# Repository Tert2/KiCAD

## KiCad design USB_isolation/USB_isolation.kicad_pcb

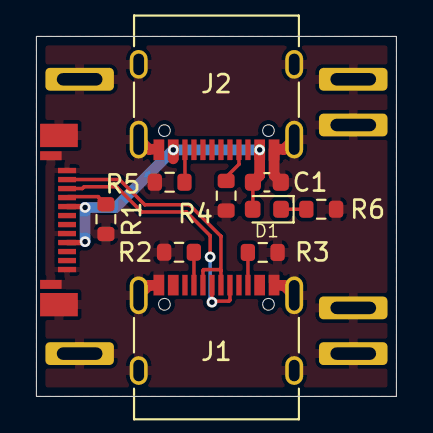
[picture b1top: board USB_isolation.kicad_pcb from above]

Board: 2 copper layers, 20.0 x 20.0 mm, 13 parts (0 on the bottom side), 10 nets.

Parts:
C1: 0.1u; C_0603_1608Metric
D1: LED_Small; LED_0603_1608Metric
J1, J2: USB_C_Receptacle_USB2.0_16P; USB_C_Receptacle_XKB_U262-16XN-4BVC11
J3: Conn_01x04_Pin; 4p
J8: Conn_01x02_Pin; 2p
R1, R2, R3, R4, R5, R6: 4.7k; R_0603_1608Metric
U1: UCAM001

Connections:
+5V: C1.1, D1.2 (A), J2.A4 (VBUS), J2.A9 (VBUS), J2.B4 (VBUS), J2.B9 (VBUS), U1.A4 (VBUS), U1.B9 (VBUS)
/D+: J1.A6 (D+), J1.B6 (D+), U1.A6 (D+)
/D-: J1.A7 (D-), J1.B7 (D-), U1.A7 (D-)
GND: C1.2, J1.A1 (GND), J1.A12 (GND), J1.B1 (GND), J1.B12 (GND), J1.S1 (SHIELD), J2.A1 (GND), J2.A12 (GND), J2.B1 (GND), J2.B12 (GND), J2.S1 (SHIELD), J3.1, J3.2, J3.3, J3.4, J8.1, J8.2, R1.2, R2.2, R3.2, R4.2, R5.2, R6.2, U1.A1 (GND), U1.A12 (GND), U1.B12 (GND), U1.S1 (SHIELD), U1.S2 (SHIELD)
unnamed: D1.1 (K), R6.1
unnamed: J1.A5 (CC1), R2.1
unnamed: J1.B5 (CC2), R3.1
unnamed: J2.A5 (CC1), R4.1
unnamed: J2.B5 (CC2), R5.1
unnamed: R1.1, U1.A5 (CC1)

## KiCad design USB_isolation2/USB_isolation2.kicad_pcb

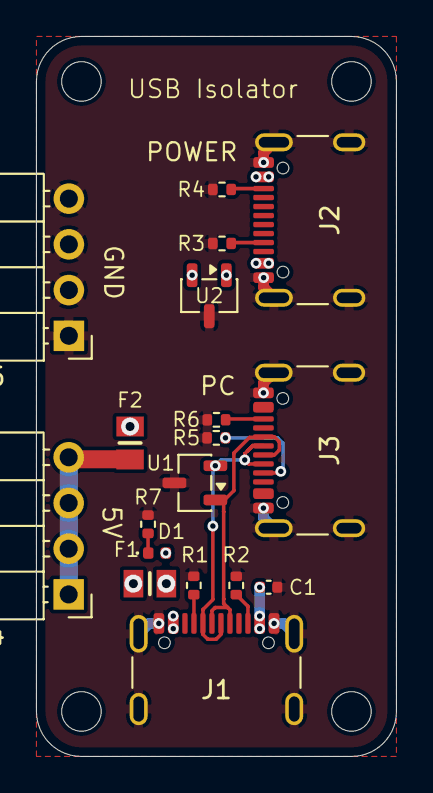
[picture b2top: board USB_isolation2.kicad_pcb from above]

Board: 2 copper layers, 20.0 x 40.0 mm, 18 parts (0 on the bottom side), 13 nets.

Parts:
C1: 4.7u; C_0402_1005Metric
D1: LED_Small; LED_0402_1005Metric
F1, F2: PICOSMDC110S-2; PICOSMDC010S2
J1, J2, J3: USB_C_Receptacle_USB2.0_16P; USB_C_Receptacle_GCT_USB4105-xx-A_16P_TopMnt_Horizontal
J4, J5: Conn_01x04_Pin; PinHeader_1x04_P2.54mm_Horizontal
R1, R2, R3, R4, R5, R6, R7: 4.7k; R_0402_1005Metric
U1, U2: SOT-23-3

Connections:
+5V: C1.1, D1.2 (A), F1.1, J1.A4 (VBUS), J1.A9 (VBUS), J1.B4 (VBUS), J1.B9 (VBUS)
D+: J1.A6 (D+), J1.B6 (D+), J3.A6 (D+), J3.B6 (D+), U1.1
D-: J1.A7 (D-), J1.B7 (D-), J3.A7 (D-), J3.B7 (D-), U1.2
GND: C1.2, J1.A1 (GND), J1.A12 (GND), J1.B1 (GND), J1.B12 (GND), J1.S1 (SHIELD), J2.A1 (GND), J2.A12 (GND), J2.B1 (GND), J2.B12 (GND), J2.S1 (SHIELD), J3.A1 (GND), J3.A12 (GND), J3.B1 (GND), J3.B12 (GND), J3.S1 (SHIELD), J5.1, J5.2, J5.3, J5.4, R1.2, R2.2, R3.2, R4.2, R5.2, R6.2, R7.2, U1.3, U2.3
unnamed: D1.1 (K), R7.1
unnamed: J1.A5 (CC1), R1.1
unnamed: J1.B5 (CC2), R2.1
unnamed: J2.A5 (CC1), R3.1
unnamed: J2.B5 (CC2), R4.1
unnamed: J3.A5 (CC1), R5.1
unnamed: J3.B5 (CC2), R6.1
unnamed: F2.2, J4.1, J4.2, J4.3, J4.4
VBUS: F1.2, F2.1, J2.A4 (VBUS), J2.A9 (VBUS), J2.B4 (VBUS), J2.B9 (VBUS), U2.1, U2.2

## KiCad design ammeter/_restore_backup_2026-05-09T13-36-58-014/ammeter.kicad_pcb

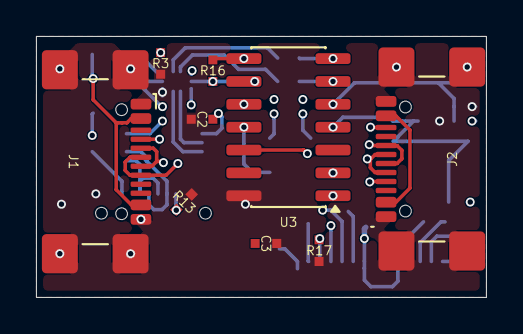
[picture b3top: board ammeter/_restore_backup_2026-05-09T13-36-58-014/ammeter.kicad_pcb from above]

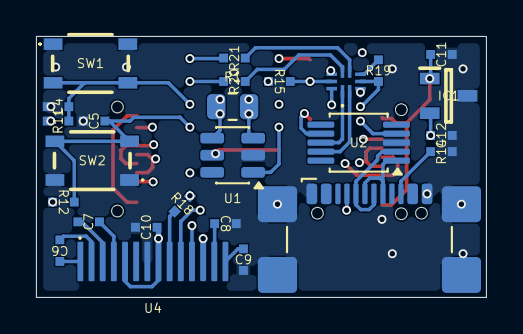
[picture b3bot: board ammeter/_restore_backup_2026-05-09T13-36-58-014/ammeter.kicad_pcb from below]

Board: 4 copper layers, 25.0 x 14.5 mm, 35 parts (26 on the bottom side), 36 nets.

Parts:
C2, C3, C4, C5: 0.1u; 1005
C6, C7, C8, C11: 1u; 1005
C9, C10: 4.7u; 1005
C12: 10u; 1005
IC1: AP7375-33SA-7; SOT96P240X110-3N
IC2: TMUXHS221NKGT
J1, J2, J3: USB_C_Receptacle_USB2.0_16P; USB_C_Receptacle_GCT_USB4110
R1: 8m; R_0805_2012Metric
R3, R11, R12, R18: 10k; R1005
R13, R14, R15, R16, R19, R20, R21: 4.7k; R1005
R17: 100k; R1005
SW1, SW2: SW_MEC_5E; SKRPABE010
U1: INA181; SOT-23-6
U2: CH340E; MSOP-10_3x3mm_P0.5mm
U3: ATtiny1604-SS; SOIC-14_3.9x8.7mm_P1.27mm
U4: X032-6032TSWAG02-H14 F

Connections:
+3V3: C2.1, C10.1, C12.1, IC1.2 (VOUT), IC2.9 (VCC), R11.2, R12.2, R15.2, R16.2, R18.2, U1.6 (V+), U2.7 (VCC), U2.10 (V3), U3.1 (VCC), U4.5 (VBAT), U4.8 (Vdd)
/#RTS: IC2.10 (SEL), U2.4 (~RTS)
/#res: R18.1, U4.9 (#RES)
/D+: J3.A6 (D+), J3.B6 (D+), U2.1 (UD+)
/D-: J3.A7 (D-), J3.B7 (D-), U2.2 (UD-)
/Rx: IC2.2 (D-), U2.9 (RXD)
/Rx3: R20.2, U3.6 (PB3)
/SCL: R15.1, U3.9 (PB0), U4.10 (SCL)
/SDA: R16.1, U3.8 (PB1), U4.11 (SDA)
/Tx: IC2.1 (D+), U2.8 (TXD)
/Tx2: R21.2, U3.7 (PB2)
/UPDI: IC2.4 (DA-), R19.2, U3.10 (~RESET/PA0)
/V0: U1.1, U3.11 (PA1)
/V1: C3.2, U1.5 (REF), U3.12 (PA2)
/ref: J2.A4 (VBUS), J2.A9 (VBUS), J2.B4 (VBUS), J2.B9 (VBUS), R1.1, U1.4 (-)
/sw1: C4.2, R11.1, SW1.3 (K), SW1.4 (A), U3.5 (PA7)
/sw2: C5.2, R12.1, SW2.3 (K), SW2.4 (A), U3.4 (PA6)
GND: C2.2, C3.1, C4.1, C5.1, C8.2, C9.2, C10.2, C11.1, C12.2, IC1.3 (GND), IC2.3 (GND), J1.A1 (GND), J1.A12 (GND), J1.B1 (GND), J1.B12 (GND), J1.SH (SHIELD), J2.A1 (GND), J2.A12 (GND), J2.B1 (GND), J2.B12 (GND), J2.SH (SHIELD), J3.A1 (GND), J3.A12 (GND), J3.B1 (GND), J3.B12 (GND), J3.SH (SHIELD), R3.2, R13.2, R14.2, R17.2, SW1.1, SW1.2, SW2.1, SW2.2, U1.2 (GND), U2.3 (GND), U3.14 (GND), U4.7 (Vss)
unnamed: IC2.5 (DA+), R19.1
unnamed: IC2.7 (DB+), R20.1
unnamed: IC2.6 (DB-), R21.1
unnamed: IC2.8 (OEN), R3.1
unnamed: J1.A5 (CC1), J2.A5 (CC1)
unnamed: J1.B5 (CC2), J2.B5 (CC2)
unnamed: J1.A6 (D+), J1.B6 (D+), J2.A6 (D+), J2.B6 (D+)
unnamed: J1.A7 (D-), J1.B7 (D-), J2.A7 (D-), J2.B7 (D-)
unnamed: J3.A5 (CC1), R13.1
unnamed: J3.B5 (CC2), R14.1
unnamed: C7.2, U4.4 (C1N)
unnamed: C7.1, U4.3 (C1P)
unnamed: C6.2, U4.2 (C2N)
unnamed: C6.1, U4.1 (C2P)
unnamed: R17.1, U4.12 (IREF)
unnamed: C8.1, U4.13 (VCOMH)
unnamed: C9.1, U4.14 (Vcc)
VBUS: C11.2, IC1.1 (VIN), J1.A4 (VBUS), J1.A9 (VBUS), J1.B4 (VBUS), J1.B9 (VBUS), R1.2, U1.3 (+)

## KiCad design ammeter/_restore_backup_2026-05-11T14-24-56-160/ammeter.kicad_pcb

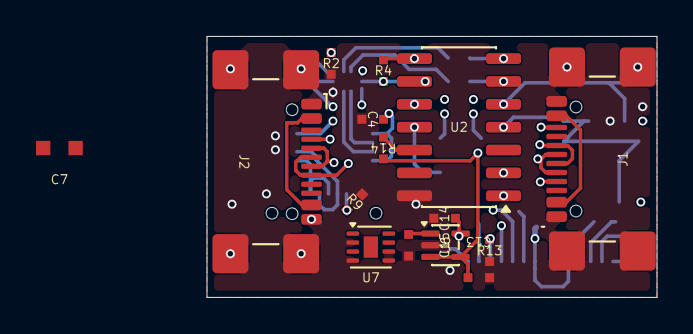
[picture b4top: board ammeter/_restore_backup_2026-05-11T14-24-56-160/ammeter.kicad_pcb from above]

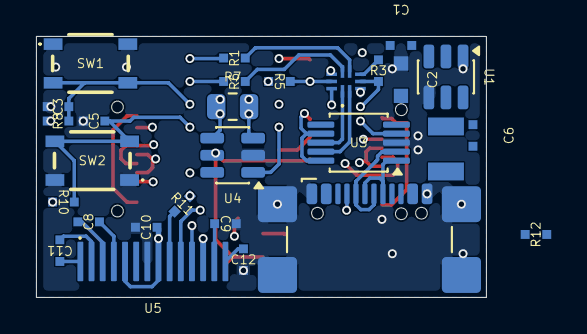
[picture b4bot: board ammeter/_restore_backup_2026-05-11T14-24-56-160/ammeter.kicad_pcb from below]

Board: 4 copper layers, 25.0 x 14.5 mm, 43 parts (28 on the bottom side), 41 nets.

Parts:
C1: 10u; 1005
C2, C7: 22u; C1608
C3, C4, C5, C6, C13: 0.1u; 1005
C8, C9, C11, C14: 1u; 1005
C10, C12: 4.7u; 1005
C15: 1n; 1005
IC1: TMUXHS221NKGT
J1, J2, J3: USB_C_Receptacle_USB2.0_16P; USB_C_Receptacle_GCT_USB4110
L1: 4.7uH; C2520
R1, R3, R4, R5, R6, R9, R12: 4.7k; R1005
R2, R8, R10, R11: 10k; R1005
R7: 8m; R_0805_2012Metric
R13: 100k; R1005
R14: 100; R1005
SW1, SW2: SW_MEC_5E; SKRPABE010
U1: AP63203WU; TSOT-23-6
U2: ATtiny1604-SS; SOIC-14_3.9x8.7mm_P1.27mm
U3: CH340E; MSOP-10_3x3mm_P0.5mm
U4: INA181; SOT-23-6
U5: X032-6032TSWAG02-H14 F
U6: TLV9001IDCK; SOT-353_SC-70-5
U7: MCP1501-12xRW; WDFN-8-1EP_2x2mm_P0.5mm_EP0.8x1.2mm

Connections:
+3V3: C2.1, C4.1, C6.1, C7.1, C10.1, C14.2, IC1.9 (VCC), L1.1, R4.2, R5.2, R8.2, R10.2, R11.2, U1.5 (SW), U2.1 (VCC), U3.7 (VCC), U3.10 (V3), U4.6 (V+), U5.5 (VBAT), U5.8 (Vdd), U6.5 (V+), U7.1 (VDD), U7.3 (~SHDN)
/#RTS: IC1.10 (SEL), U3.4 (~RTS)
/#res: R11.1, U5.9 (#RES)
/D+: J3.A6 (D+), J3.B6 (D+), U3.1 (UD+)
/D-: J3.A7 (D-), J3.B7 (D-), U3.2 (UD-)
/Rx: IC1.2 (D-), U3.9 (RXD)
/Rx3: R6.2, U2.6 (PB3)
/SCL: R5.1, U2.9 (PB0), U5.10 (SCL)
/SDA: R4.1, U2.8 (PB1), U5.11 (SDA)
/Tx: IC1.1 (D+), U3.8 (TXD)
/Tx2: R1.2, U2.7 (PB2)
/UPDI: IC1.4 (DA-), R3.2, U2.10 (~RESET/PA0)
/V0: U2.11 (PA1), U4.1
/V1: R14.2, U2.12 (PA2)
/Vshunt: J3.A8 (SBU1), U2.13 (PA3)
/ref: J1.A4 (VBUS), J1.A9 (VBUS), J1.B4 (VBUS), J1.B9 (VBUS), R7.1, U4.4 (-)
/sw1: C3.2, R8.1, SW1.3 (K), SW1.4 (A), U2.5 (PA7)
/sw2: C5.2, R10.1, SW2.3 (K), SW2.4 (A), U2.4 (PA6)
GND: C1.2, C2.2, C3.1, C4.2, C5.1, C7.2, C9.2, C10.2, C12.2, C13.1, C14.1, C15.1, IC1.3 (GND), J1.A1 (GND), J1.A12 (GND), J1.B1 (GND), J1.B12 (GND), J1.SH (SHIELD), J2.A1 (GND), J2.A12 (GND), J2.B1 (GND), J2.B12 (GND), J2.SH (SHIELD), J3.A1 (GND), J3.A12 (GND), J3.B1 (GND), J3.B12 (GND), J3.SH (SHIELD), R2.2, R9.2, R12.2, R13.2, SW1.1, SW1.2, SW2.1, SW2.2, U1.4 (GND), U2.14 (GND), U3.3 (GND), U4.2 (GND), U5.7 (Vss), U6.2 (V-), U7.2 (GND), U7.4 (GND), U7.5 (GND), U7.6 (GND)
unnamed: IC1.5 (DA+), R3.1
unnamed: IC1.7 (DB+), R6.1
unnamed: IC1.6 (DB-), R1.1
unnamed: IC1.8 (OEN), R2.1
unnamed: J1.A5 (CC1), J2.A5 (CC1)
unnamed: J1.B5 (CC2), J2.B5 (CC2)
unnamed: J1.A6 (D+), J1.B6 (D+), J2.A6 (D+), J2.B6 (D+)
unnamed: J1.A7 (D-), J1.B7 (D-), J2.A7 (D-), J2.B7 (D-)
unnamed: J3.A5 (CC1), R9.1
unnamed: J3.B5 (CC2), R12.1
unnamed: C13.2, R14.1, U4.5 (REF), U6.3 (-), U6.4
unnamed: C8.2, U5.4 (C1N)
unnamed: C8.1, U5.3 (C1P)
unnamed: C11.2, U5.2 (C2N)
unnamed: C11.1, U5.1 (C2P)
unnamed: R13.1, U5.12 (IREF)
unnamed: C9.1, U5.13 (VCOMH)
unnamed: C12.1, U5.14 (Vcc)
unnamed: C6.2, U1.6 (BST)
unnamed: L1.2, U1.1 (FB)
unnamed: C15.2, U6.1 (+), U7.7 (OUT), U7.8 (FB)
VBUS: C1.1, J2.A4 (VBUS), J2.A9 (VBUS), J2.B4 (VBUS), J2.B9 (VBUS), R7.2, U1.2 (EN), U1.3 (IN), U4.3 (+)

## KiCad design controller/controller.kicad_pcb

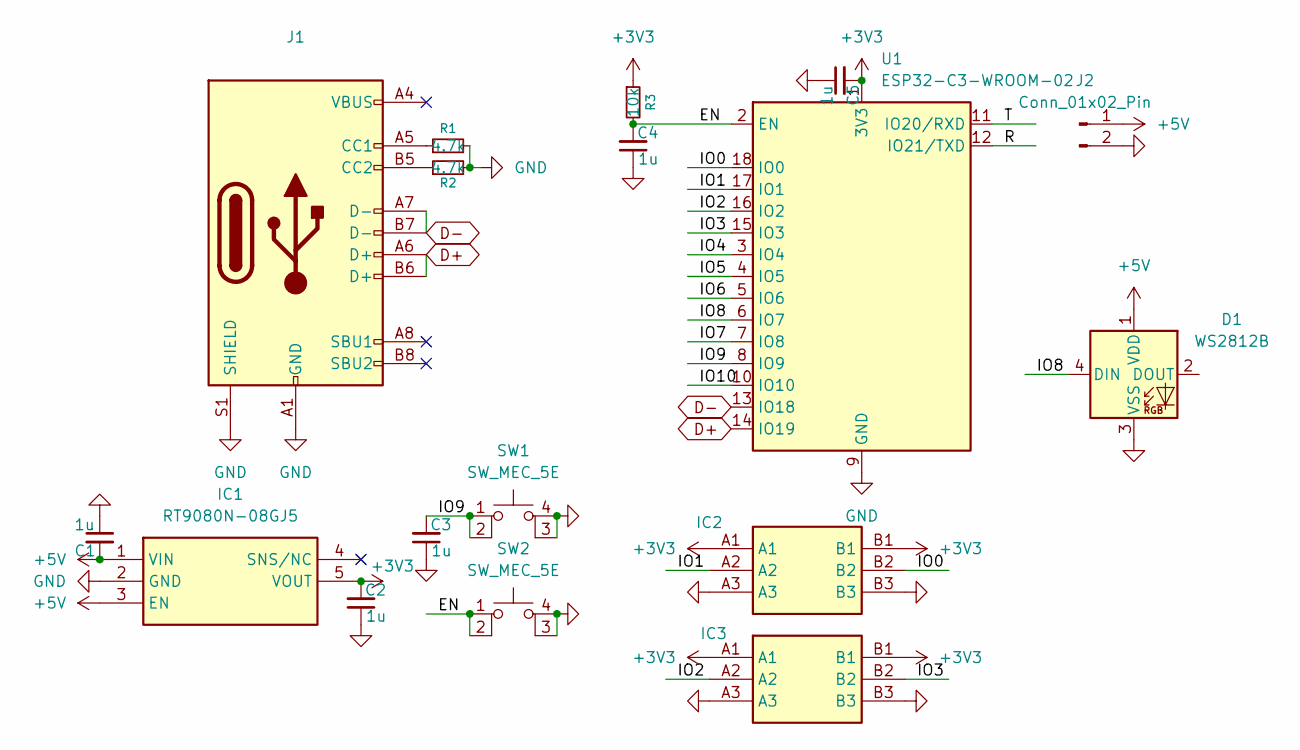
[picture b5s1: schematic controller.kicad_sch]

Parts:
C1, C2, C3, C4, C5: 1u; C_0603_1608Metric
D1: WS2812B; LED_WS2812B_PLCC4_5.0x5.0mm_P3.2mm
IC1: RT9080N-08GJ5; SOT94P280X100-5N; Manufacturer_Part_Number RT9080N-08GJ5; Mouser Part Number 835-RT9080N-08GJ5
IC2, IC3: JT8P-3.2T-B10K-1-16Y; JT8P32TB10K116Y; Manufacturer_Part_Number JT8P-3.2T-B10K-1-16Y
J1: USB_C_Receptacle_USB2.0_16P; USB_C_Receptacle_GCT_USB4105-xx-A_16P_TopMnt_Horizontal
J2: Conn_01x02_Pin; BAT_PAD
R1, R2: 4.7k; R_0603_1608Metric
R3: 10k; R_0603_1608Metric
SW1, SW2: SW_MEC_5E; SW_SKRPABE010
U1: ESP32-C3-WROOM-02

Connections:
+3V3: C2.2, C5.2, IC1.5 (VOUT), IC2.A1, IC2.B1, IC3.A1, IC3.B1, R3.1, U1.1 (3V3)
+5V: C1.2, D1.1 (VDD), IC1.1 (VIN), IC1.3 (EN), J2.1
/EN: C4.2, R3.2, SW2.1, SW2.2, U1.2 (EN)
/IO0: IC2.B2, U1.18 (IO0)
/IO1: IC2.A2, U1.17 (IO1)
/IO2: IC3.A2, U1.16 (IO2)
/IO3: IC3.B2, U1.15 (IO3)
/IO4: U1.3 (IO4)
/IO5: U1.4 (IO5)
/IO6: U1.5 (IO6)
/IO7: U1.7 (IO8)
/IO8: D1.4 (DIN), U1.6 (IO7)
/IO9: C3.2, SW1.1, SW1.2, U1.8 (IO9)
/IO10: U1.10 (IO10)
/R: U1.12 (IO21/TXD)
/T: U1.11 (IO20/RXD)
D+: J1.A6 (D+), J1.B6 (D+), U1.14 (IO19)
D-: J1.A7 (D-), J1.B7 (D-), U1.13 (IO18)
GND: C1.1, C2.1, C3.1, C4.1, C5.1, D1.3 (VSS), IC1.2 (GND), IC2.A3, IC2.B3, IC3.A3, IC3.B3, J1.A1 (GND), J1.A12 (GND), J1.B1 (GND), J1.B12 (GND), J1.S1 (SHIELD), J2.2, R1.2, R2.2, SW1.3 (K), SW1.4 (A), SW2.3 (K), SW2.4 (A), U1.9 (GND), U1.19 (GND)
unnamed: J1.A5 (CC1), R1.1
unnamed: J1.B5 (CC2), R2.1

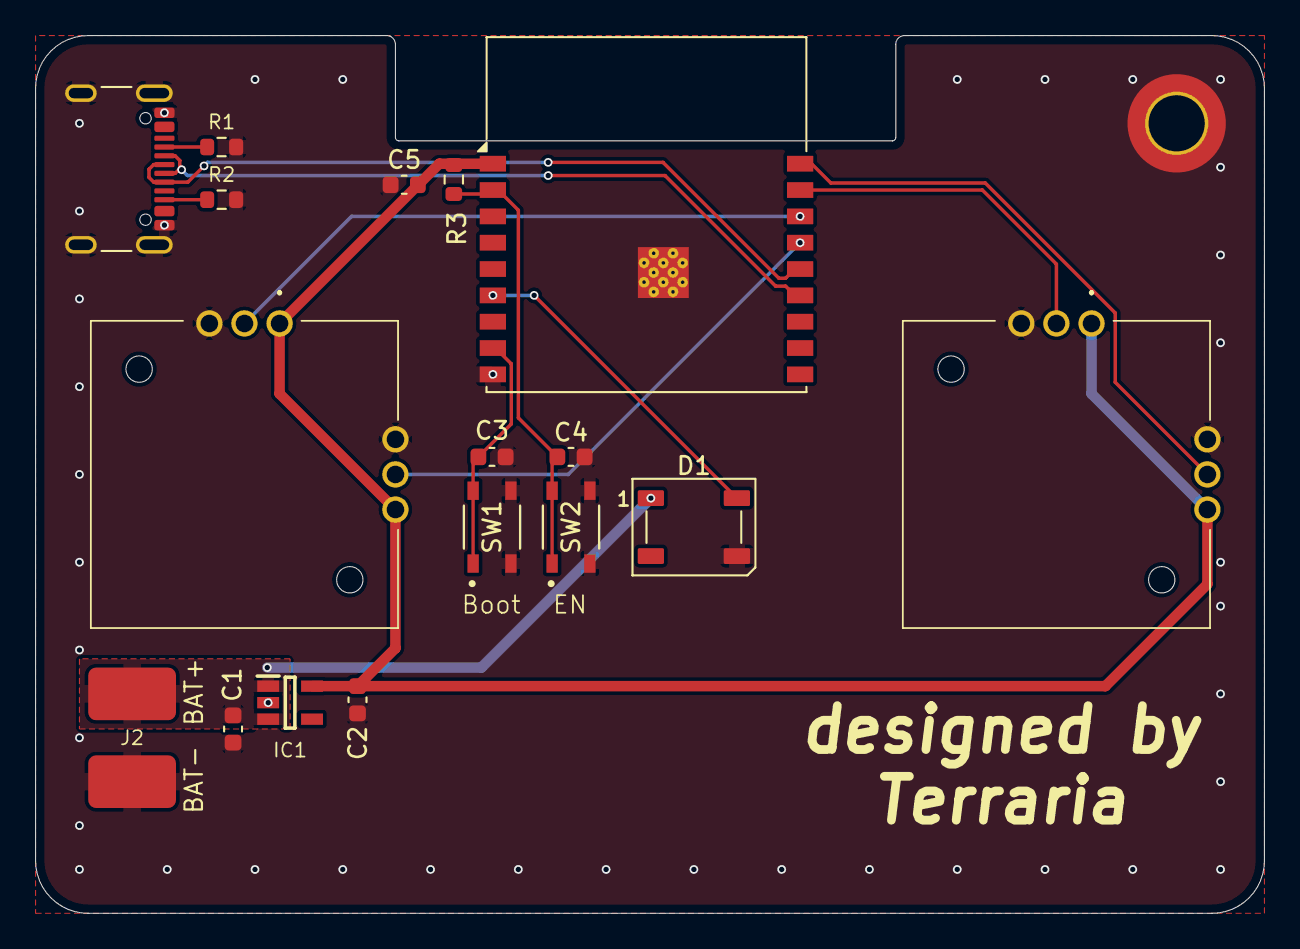
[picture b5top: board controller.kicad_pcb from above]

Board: 2 copper layers, 70.0 x 50.0 mm, 17 parts (0 on the bottom side), 14 nets.
